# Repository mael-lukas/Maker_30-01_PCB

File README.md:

# Maker_30-01_PCB
Schematic and PCB exercise for Maker 30/01 class

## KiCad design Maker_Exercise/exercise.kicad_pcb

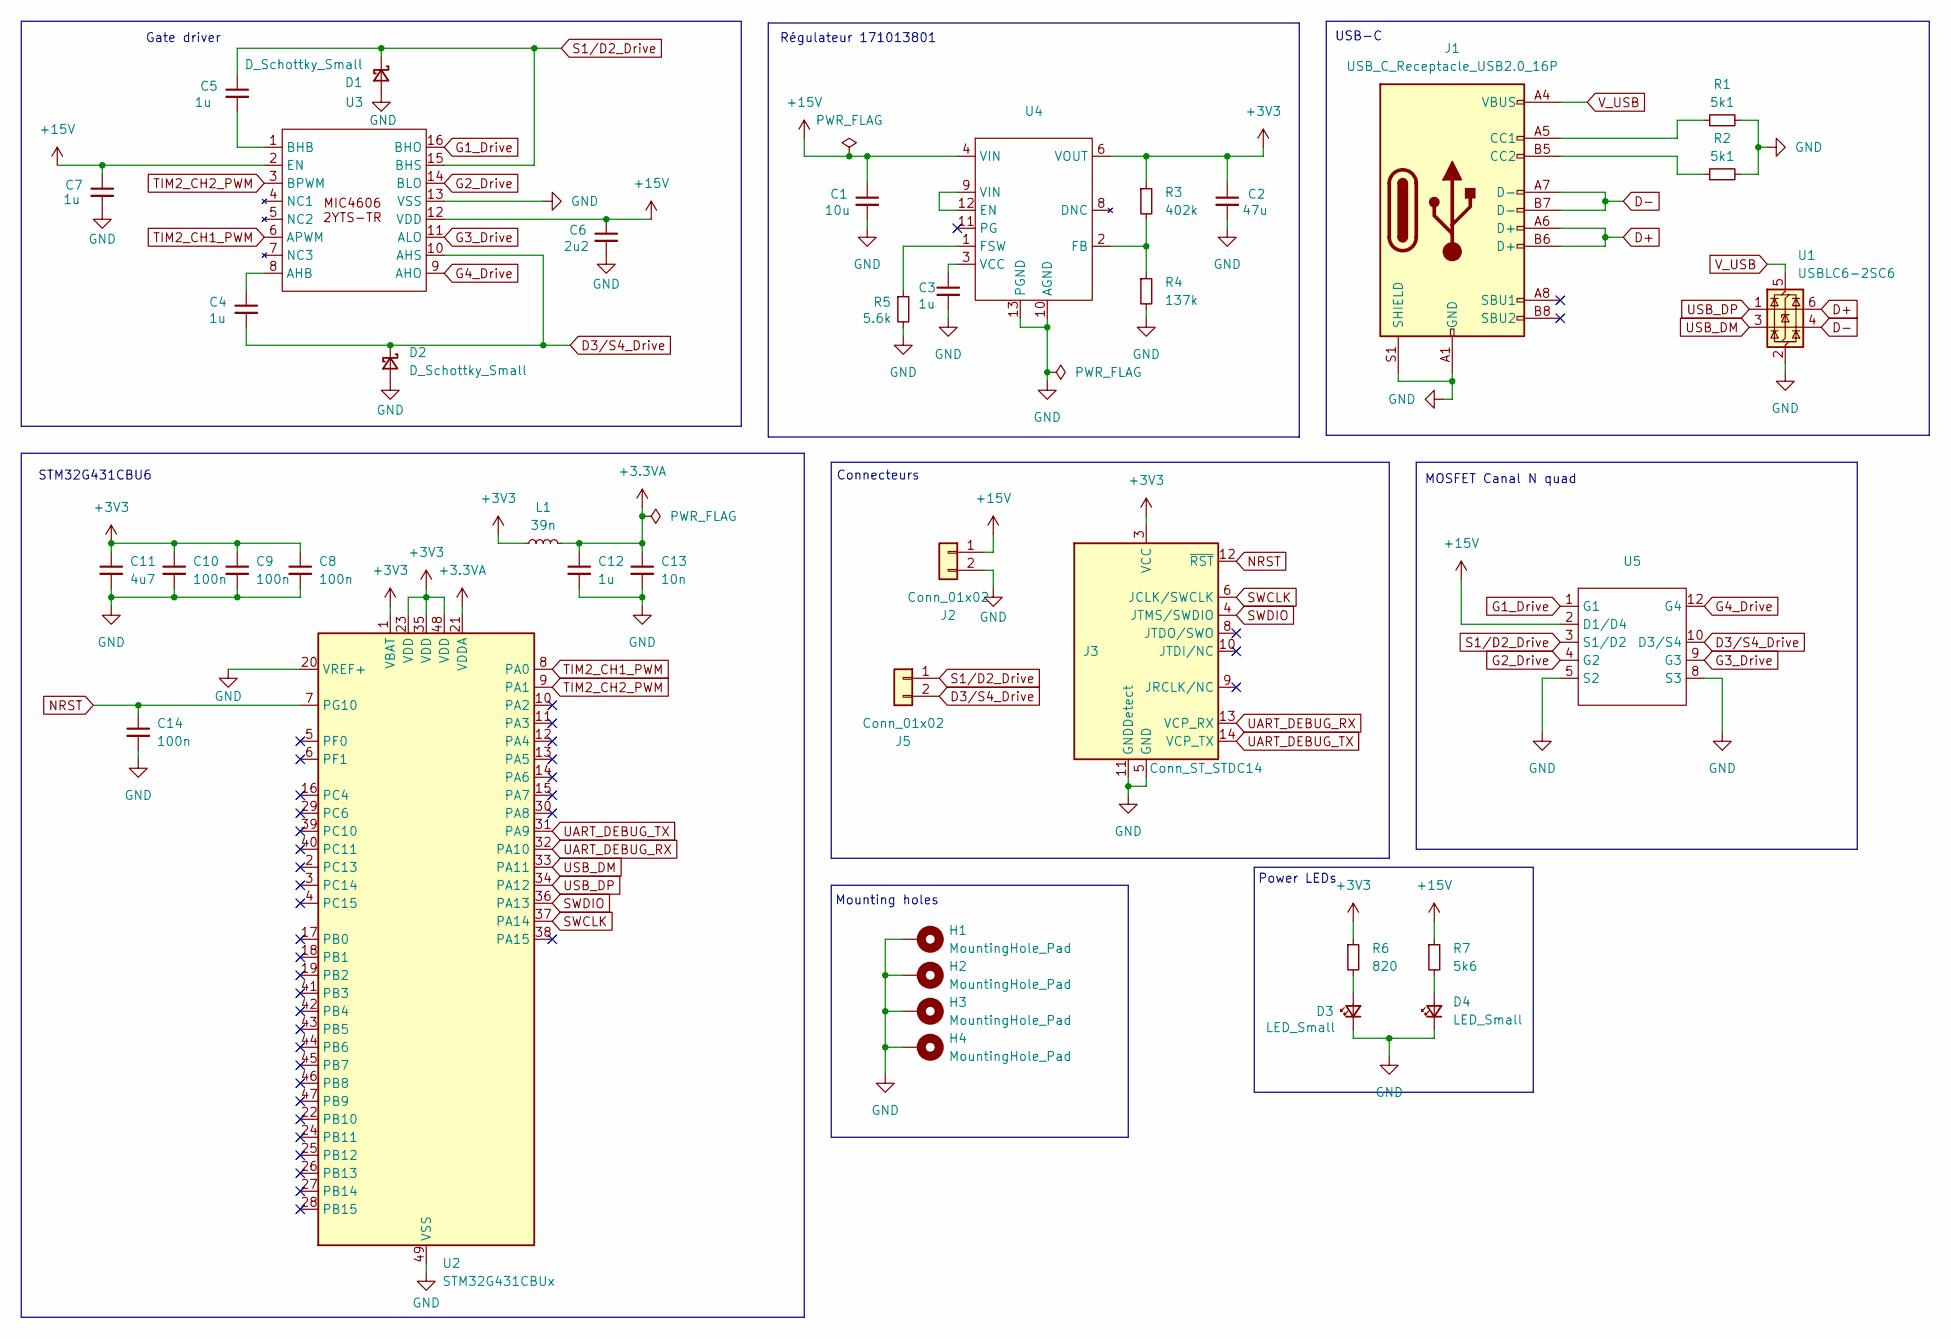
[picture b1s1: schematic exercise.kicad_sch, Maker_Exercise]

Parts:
C1: 10u; C_0402_1005Metric_Pad0.74x0.62mm_HandSolder
C2: 47u; C_0402_1005Metric_Pad0.74x0.62mm_HandSolder
C3, C4, C5, C7, C12: 1u; C_0402_1005Metric_Pad0.74x0.62mm_HandSolder
C6: 2u2; C_0402_1005Metric_Pad0.74x0.62mm_HandSolder
C8, C9, C10, C14: 100n; C_0402_1005Metric_Pad0.74x0.62mm_HandSolder
C11: 4u7; C_0402_1005Metric_Pad0.74x0.62mm_HandSolder
C13: 10n; C_0402_1005Metric_Pad0.74x0.62mm_HandSolder
D1, D2: D_Schottky_Small; D_0603_1608Metric_Pad1.05x0.95mm_HandSolder
D3, D4: LED_Small; LED_0603_1608Metric_Pad1.05x0.95mm_HandSolder
H1, H2, H3, H4: MountingHole_Pad; MountingHole_3.2mm_M3_DIN965_Pad
J1: USB_C_Receptacle_USB2.0_16P; USB_C_Receptacle_G-Switch_GT-USB-7010ASV
J2: Conn_01x02; AMASS_XT60-M_1x02_P7.20mm_Vertical
J3: Conn_ST_STDC14; PinHeader_2x07_P1.27mm_Vertical_SMD
J5: Conn_01x02; JST_EH_B2B-EH-A_1x02_P2.50mm_Vertical
L1: 39n; L_0805_2012Metric_Pad1.05x1.20mm_HandSolder
R1, R2: 5k1; R_0402_1005Metric_Pad0.72x0.64mm_HandSolder
R3: 402k; R_0402_1005Metric_Pad0.72x0.64mm_HandSolder
R4: 137k; R_0402_1005Metric_Pad0.72x0.64mm_HandSolder
R5: 5.6k; R_0402_1005Metric_Pad0.72x0.64mm_HandSolder
R6: 820; R_0402_1005Metric_Pad0.72x0.64mm_HandSolder
R7: 5k6; R_0402_1005Metric_Pad0.72x0.64mm_HandSolder
U1: USBLC6-2SC6; SOT-23-6
U2: STM32G431CBUx; QFN-48-1EP_7x7mm_P0.5mm_EP5.6x5.6mm; MPN STM32G431CBU6
U3: TSSOP-16_4.4x5mm_P0.65mm
U4: Regulator_171013801; MPN 171013801
U5: FDMQ86530L; MPN FDMQ86530L

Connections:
+3.3VA: C12.1, C13.1, L1.2, U2.21 (VDDA)
+3V3: C2.1, C8.1, C9.1, C10.1, C11.1, J3.3 (VCC), L1.1, R3.1, R6.1, U2.1 (VBAT), U2.23 (VDD), U2.35 (VDD), U2.48 (VDD), U4.6 (VOUT), U4.7 (VOUT)
+15V: C1.1, C6.1, C7.1, J2.1, R7.1, U3.2 (EN), U3.12 (VDD), U4.4 (VIN), U4.5 (VIN), U5.2 (D1/D4), U5.11 (D1/D4), U5.13 (D1/D4)
D3/S4_Drive: C4.2, D2.1 (K), J5.2, U3.10 (AHS), U5.10 (D3/S4), U5.15 (D3/S4)
D+: J1.A6 (D+), J1.B6 (D+), U1.6 (I/O1)
D-: J1.A7 (D-), J1.B7 (D-), U1.4 (I/O2)
G1_Drive: U3.16 (BHO), U5.1 (G1)
G2_Drive: U3.14 (BLO), U5.4 (G2)
G3_Drive: U3.11 (ALO), U5.9 (G3)
G4_Drive: U3.9 (AHO), U5.12 (G4)
GND: C1.2, C2.2, C3.2, C6.2, C7.2, C8.2, C9.2, C10.2, C11.2, C12.2, C13.2, C14.2, D1.2 (A), D2.2 (A), D3.1 (K), D4.1 (K), H1.1, H2.1, H3.1, H4.1, J1.A1 (GND), J1.A12 (GND), J1.B1 (GND), J1.B12 (GND), J1.S1 (SHIELD), J2.2, J3.5 (GND), J3.7 (GND), J3.11 (GNDDetect), R1.2, R2.2, R4.2, R5.2, U1.2 (GND), U2.20 (VREF+), U2.49 (VSS), U3.13 (VSS), U4.10 (AGND), U4.13 (PGND), U5.5 (S2), U5.6 (S2), U5.7 (S3), U5.8 (S3)
NRST: C14.1, J3.12 (~RST), U2.7 (PG10)
unnamed: D3.2 (A), R6.2
unnamed: D4.2 (A), R7.2
unnamed: J1.A5 (CC1), R1.1
unnamed: J1.B5 (CC2), R2.1
unnamed: C4.1, U3.8 (AHB)
unnamed: C5.2, U3.1 (BHB)
unnamed: U4.9 (VIN), U4.12 (EN)
unnamed: R3.2, R4.1, U4.2 (FB)
unnamed: R5.1, U4.1 (FSW)
unnamed: C3.1, U4.3 (VCC)
S1/D2_Drive: C5.1, D1.1 (K), J5.1, U3.15 (BHS), U5.3 (S1/D2), U5.14 (S1/D2)
SWCLK: J3.6 (JCLK/SWCLK), U2.37 (PA14)
SWDIO: J3.4 (JTMS/SWDIO), U2.36 (PA13)
TIM2_CH1_PWM: U2.8 (PA0), U3.6 (APWM)
TIM2_CH2_PWM: U2.9 (PA1), U3.3 (BPWM)
UART_DEBUG_RX: J3.13 (VCP_RX), U2.32 (PA10)
UART_DEBUG_TX: J3.14 (VCP_TX), U2.31 (PA9)
USB_DM: U1.3 (I/O2), U2.33 (PA11)
USB_DP: U1.1 (I/O1), U2.34 (PA12)
V_USB: J1.A4 (VBUS), J1.A9 (VBUS), J1.B4 (VBUS), J1.B9 (VBUS), U1.5 (VBUS)

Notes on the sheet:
MOSFET Canal N quad
Gate driver
Mounting holes
STM32G431CBU6
Connecteurs
Régulateur 171013801
Power LEDs
USB-C

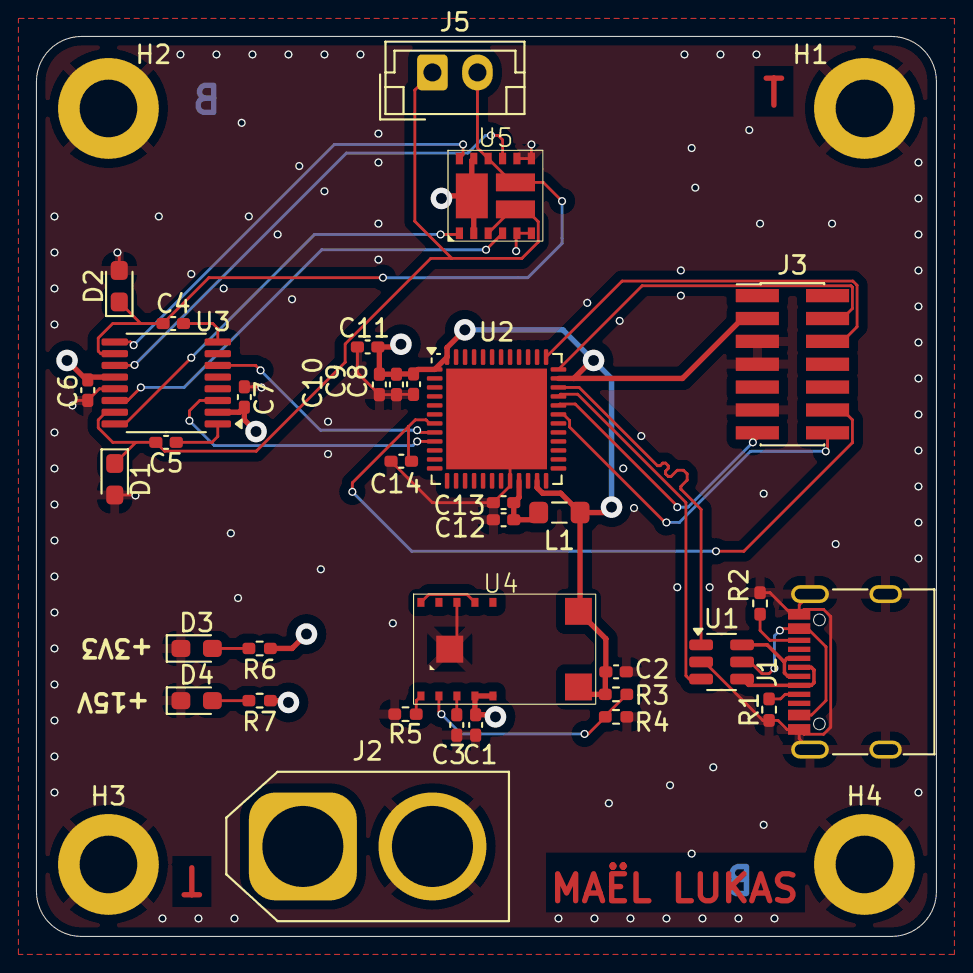
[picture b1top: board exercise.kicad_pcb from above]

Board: 4 copper layers, 50.0 x 50.0 mm, 39 parts (0 on the bottom side), 32 nets.

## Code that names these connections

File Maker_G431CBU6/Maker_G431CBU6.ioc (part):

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Mcu.Name=STM32G431C(6-8-B)Ux
Mcu.Package=UFQFPN48
Mcu.UserName=STM32G431C6Ux
PA0.Signal=S_TIM2_CH1
PA1.Signal=S_TIM2_CH2
PA10.GPIOParameters=GPIO_Label
PA10.GPIO_Label=UART_DEBUG_RX
PA10.Mode=Asynchronous
PA10.Signal=USART1_RX
PA11.Mode=Device
PA11.Signal=USB_DM
PA12.Mode=Device
PA12.Signal=USB_DP
PA13.Mode=Serial_Wire
PA13.Signal=SYS_JTMS-SWDIO
PA14.Mode=Serial_Wire
PA14.Signal=SYS_JTCK-SWCLK
PA9.GPIOParameters=GPIO_Label
PA9.GPIO_Label=UART_DEBUG_TX
PA9.Mode=Asynchronous
PA9.Signal=USART1_TX
RCC.HSE_VALUE=8000000
RCC.SYSCLKFreq_VALUE=16000000
board=custom

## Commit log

2025-01-30 Schematic for wurtz voltage regulator
2025-01-30 MOSFET datasheet
2025-01-30 Updated schematic
2025-01-31 finalized schematic and added custom footprints
2025-02-01 finalized PCB and routing
2025-02-03 added cubeIDE pinout for processor
